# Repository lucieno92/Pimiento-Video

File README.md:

# Suite Post-Production — Prototype

Application desktop regroupant plusieurs outils de post-production dans
une seule interface, avec une page d'accueil pour naviguer entre les
modules.

## Modules disponibles dans ce prototype

- **Téléchargement multiplateforme** : télécharge vidéos/audio depuis
  YouTube, TikTok, Facebook, Instagram, Vimeo, etc. (basé sur yt-dlp).
- **Métadonnées (rush)** : glisser un fichier vidéo pour voir toutes ses
  métadonnées techniques (codec, résolution, frame rate, profondeur de
  couleur, sous-échantillonnage chroma, pistes audio, sous-titres...),
  basé sur pymediainfo (équivalent du logiciel MediaInfo).
- **Encodeur** (type Shutter Encoder) : glisser une ou plusieurs vidéos,
  choisir une catégorie (montage, diffusion/broadcast, web, audio seul,
  suite d'images, réencapsulation), un format précis, ajuster résolution
  et frame rate (préréglages ou valeurs personnalisées), prévisualiser le
  rush sélectionné, et lancer l'encodage. Basé directement sur FFmpeg.
- **Transcription** : glisser un fichier audio/vidéo, choisir la langue,
  transcrire en local avec Whisper (faster-whisper), puis exporter en
  TXT/DOCX/PDF ou en sous-titres SRT/VTT (nombre de mots par sous-titre
  réglable). 100% autonome, aucun compte tiers requis.

## Installation

### 1. Python
Il faut Python 3.10 ou plus récent : https://www.python.org/downloads/
(cocher "Add python.exe to PATH" pendant l'installation).

### 2. FFmpeg et MediaInfo
Rien à installer séparément : les deux sont embarqués automatiquement
via les paquets Python `imageio-ffmpeg` et `pymediainfo`, installés à
l'étape suivante.

### 3. Dépendances Python
Dans le dossier du projet :

```bash
python3 -m venv venv
source venv/bin/activate        # Sur Windows : venv\Scripts\activate
pip install -r requirements.txt
```

## Lancer l'application

```bash
python3 main.py
```

Une page d'accueil s'ouvre avec une carte par module. Clique sur celui
que tu veux utiliser.

## Structure du projet

```
main.py                    -> point d'entrée, assemble les pages
core/
  ffmpeg_utils.py           -> détection FFmpeg (partagée par tous les modules)
  settings_store.py         -> préférences persistantes (registre Windows / plist Mac)
pages/
  home_page.py              -> page d'accueil avec les cartes de modules
  downloader_page.py        -> module Téléchargement multiplateforme
  mediainfo_page.py         -> module Métadonnées (type MediaInfo)
  encoder_page.py           -> module Encodeur (type Shutter Encoder)
  transcription_page.py     -> module Transcription (Whisper local)
  settings_page.py          -> paramètres avancés (dépannage FFmpeg), caché par défaut
```

## Note sur la Transcription (téléchargement de modèle)

Au premier lancement d'une transcription, Whisper télécharge le modèle
choisi (quelques centaines de Mo à plus d'1 Go selon la taille du modèle) —
il faut donc une connexion internet la première fois, sans création de
compte. Les lancements suivants avec le même modèle sont locaux et plus
rapides.

## Paramètres avancés (FFmpeg)

Dans l'immense majorité des cas, tout fonctionne sans rien configurer.
Si jamais un souci technique persiste, un petit bouton ⚙ discret en bas
à droite de la page d'accueil permet d'indiquer manuellement où se
trouve FFmpeg sur la machine. Ce n'est qu'un filet de sécurité — pas une
étape normale d'utilisation.

## Limitations connues de ce prototype

- Pas encore de file d'attente persistante pour les téléchargements.
- Pas encore de gestion de profils/préréglages sauvegardés.
- Le module Métadonnées met en avant les champs les plus utiles en
  post-prod (codec, résolution, frame rate, bit depth, chroma
  subsampling...) ; pour les caméras qui embarquent des informations
  spécifiques (profil LOG, LUT, timecode...), elles restent consultables
  dans la section "métadonnées brutes" si la caméra les a enregistrées
  dans le fichier — toutes les caméras ne le font pas systématiquement.
- Pas encore packagé en `.exe` / `.app` — pour l'instant ça se lance avec
  Python installé. `imageio-ffmpeg` et `pymediainfo` fournissent tous
  les deux des hooks PyInstaller, donc leur contenu embarqué sera
  automatiquement inclus dans l'exécutable final le moment venu.

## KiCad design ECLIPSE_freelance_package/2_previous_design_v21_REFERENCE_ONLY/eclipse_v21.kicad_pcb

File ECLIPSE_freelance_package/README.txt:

ECLIPSE - PCB design package
Breloque - August 2026

--------------------------------------------------------------------
WHAT IS IN THIS PACKAGE
--------------------------------------------------------------------

1_brief/
    ECLIPSE_PCB_brief_EN.pdf    <- START HERE. The full brief in English.
    ECLIPSE_PCB_brief_FR.pdf       Same document in French.

2_previous_design_v21_REFERENCE_ONLY/
    The KiCad project of the board I designed myself and that FAILED.
    Provided as documentation only - see the warning below.

--------------------------------------------------------------------
IMPORTANT - ABOUT THE PREVIOUS DESIGN
--------------------------------------------------------------------

The KiCad project in folder 2 is the board that was manufactured,
assembled in 5 units, and DESTROYED on first power-up.

It is included so you can see what was intended functionally, and so
you can verify for yourself the faults listed in section 4 of the
brief - several of them are measurable directly in these files.

DO NOT reuse this design as a starting point. It contains, among
other issues, a regulator enable pin tied to 12 V on a pin rated 6 V
absolute maximum, unconnected microcontroller strapping pins, and a
module footprint that cannot be inspected or reworked.

You are expected to redesign from scratch. You are entirely free on
components, architecture and values.

--------------------------------------------------------------------
HOW TO OPEN THE PREVIOUS DESIGN
--------------------------------------------------------------------

Open  eclipse_v21.kicad_pro  in KiCad (version 8 or newer).

The project is self-contained: the footprint library (eclipse.pretty)
and the symbol library (easyeda2kicad.kicad_sym) are included in the
same folder, and fp-lib-table / sym-lib-table point to them with
relative paths. Nothing else needs to be installed.

Board: 58 x 24 mm, 2 layers, FR-4, 1.6 mm.

BOM_eclipse_v21.csv and CPL_eclipse_v21.csv are the bill of materials
and pick-and-place files that were used for assembly (JLCPCB format).

--------------------------------------------------------------------
NOT INCLUDED
--------------------------------------------------------------------

- Gerber files: not included, as they describe the failed board and
  are of no use for a new design. They can be regenerated from the
  KiCad project if you want to look at them.

- Firmware: I supply it separately once the hardware is defined.

- BRELOQUE logo: high-resolution file supplied on request, for the
  silkscreen.

- LED strip datasheet: available on request. Please ask for it before
  sizing the LED channels - see the note in section 3 of the brief.

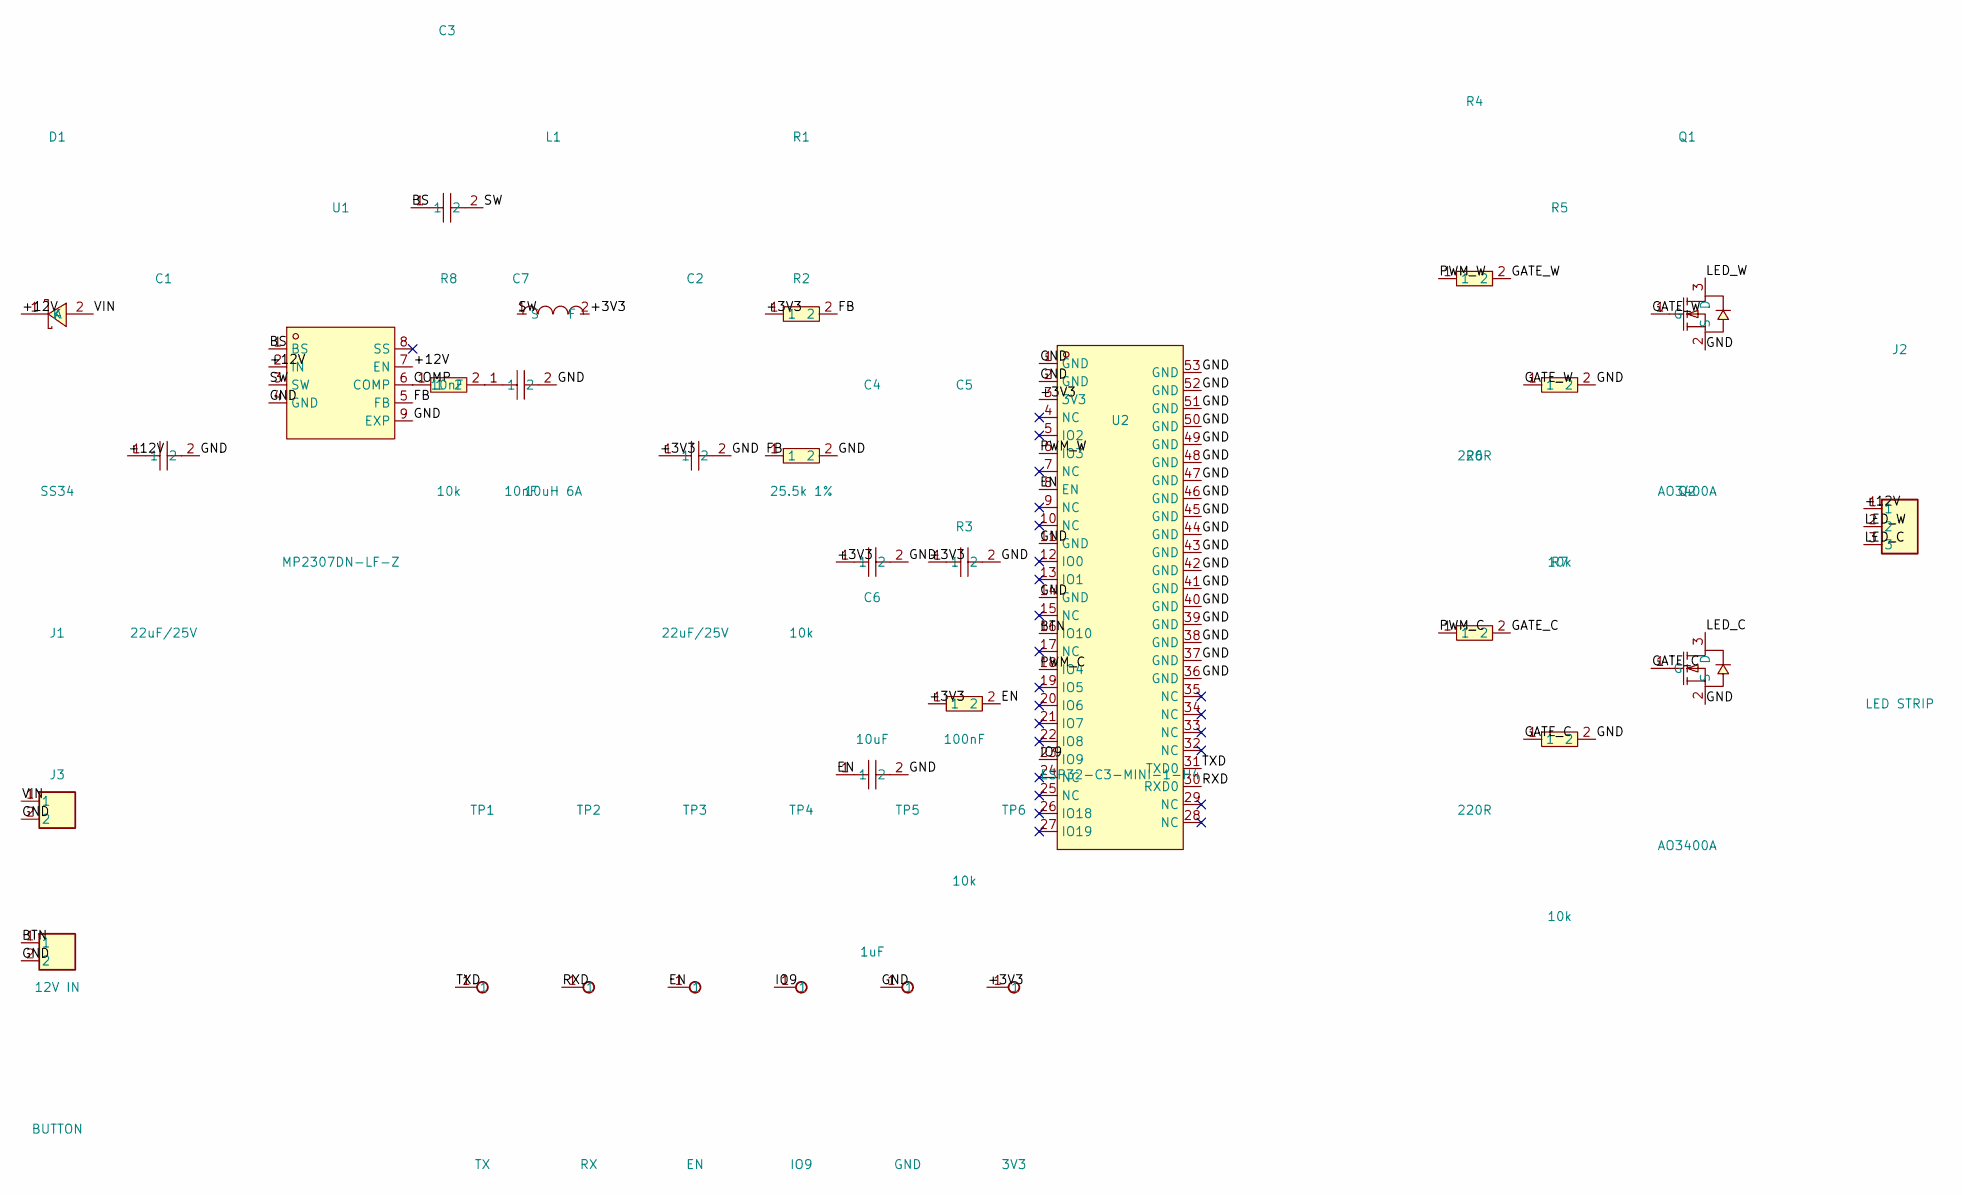
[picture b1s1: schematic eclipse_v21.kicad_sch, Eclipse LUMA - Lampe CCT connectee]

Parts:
C1: 22uF/25V; C1206; LCSC C12891
C2: 22uF/25V; C0805; LCSC C45783
C3, C7: 10nF; C0402; LCSC C15195
C4: 10uF; C0805; LCSC C15850
C5: 100nF; C0603; LCSC C14663
C6: 1uF; C0402; LCSC C52923
D1: SS34; SMA_L4.3-W2.6-LS5.2-RD; LCSC C8678
J1: 12V IN; SolderPad2
J2: LED STRIP; SolderPad3
J3: BUTTON; SolderPad2
L1: 10uH 6A; IND-SMD_L7.0-W6.6; LCSC C237927
Q1, Q2: AO3400A; SOT-23-3_L2.9-W1.3-P1.90-LS2.4-BR; LCSC C20917
R1: 25.5k 1%; R0603; LCSC C273793
R2, R3, R5, R7, R8: 10k; R0603; LCSC C25804
R4, R6: 220R; R0603; LCSC C22962
TP1: TX; TP
TP2: RX; TP
TP3: EN; TP
TP4: IO9; TP
TP5: GND; TP
TP6: 3V3; TP
U1: MP2307DN-LF-Z; SOP-8_L4.9-W3.9-P1.27-LS6.0-BL-EP; LCSC C18921
U2: ESP32-C3-MINI-1-H4; WIFIM-SMD_ESP32-C3-MINI-1; LCSC C2934569

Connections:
/+3V3: C2.1, C4.1, C5.1, L1.2 (F), R1.1, R3.1, TP6.1 (1_1), U2.3 (3V3)
/+12V: C1.1, D1.1 (K), J2.1, U1.2 (IN), U1.7 (EN)
/BS: C3.1, U1.1 (BS)
/BTN: J3.1, U2.16 (IO10)
/COMP: R8.1, U1.6 (COMP)
/EN: C6.1, R3.2, TP3.1 (1_1), U2.8 (EN)
/FB: R1.2, R2.1, U1.5 (FB)
/GATE_C: Q2.1 (G), R6.2, R7.1
/GATE_W: Q1.1 (G), R4.2, R5.1
/GND: C1.2, C2.2, C4.2, C5.2, C6.2, C7.2, J1.2, J3.2, Q1.2 (S), Q2.2 (S), R2.2, R5.2, R7.2, TP5.1 (1_1), U1.4 (GND), U1.9 (EXP), U2.1 (GND), U2.2 (GND), U2.11 (GND), U2.14 (GND), U2.36 (GND), U2.37 (GND), U2.38 (GND), U2.39 (GND), U2.40 (GND), U2.41 (GND), U2.42 (GND), U2.43 (GND), U2.44 (GND), U2.45 (GND), U2.46 (GND), U2.47 (GND), U2.48 (GND), U2.49 (GND), U2.50 (GND), U2.51 (GND), U2.52 (GND), U2.53 (GND)
/IO9: TP4.1 (1_1), U2.23 (IO9)
/LED_C: J2.3, Q2.3 (D)
/LED_W: J2.2, Q1.3 (D)
/PWM_C: R6.1, U2.18 (IO4)
/PWM_W: R4.1, U2.6 (IO3)
/RXD: TP2.1 (1_1), U2.30 (RXD0)
/SW: C3.2, L1.1 (S), U1.3 (SW)
/TXD: TP1.1 (1_1), U2.31 (TXD0)
/VIN: D1.2 (A), J1.1
unnamed: C7.1, R8.2

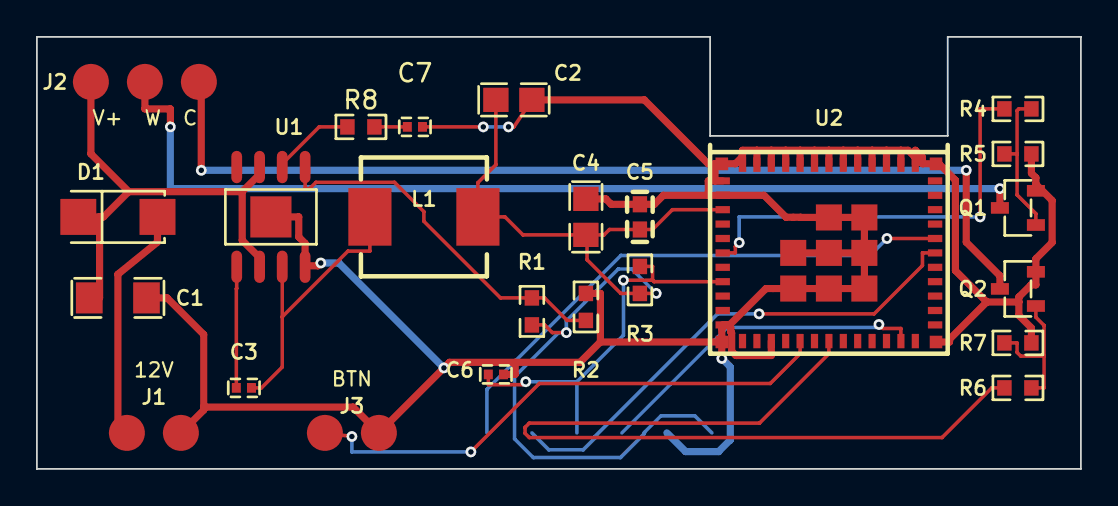
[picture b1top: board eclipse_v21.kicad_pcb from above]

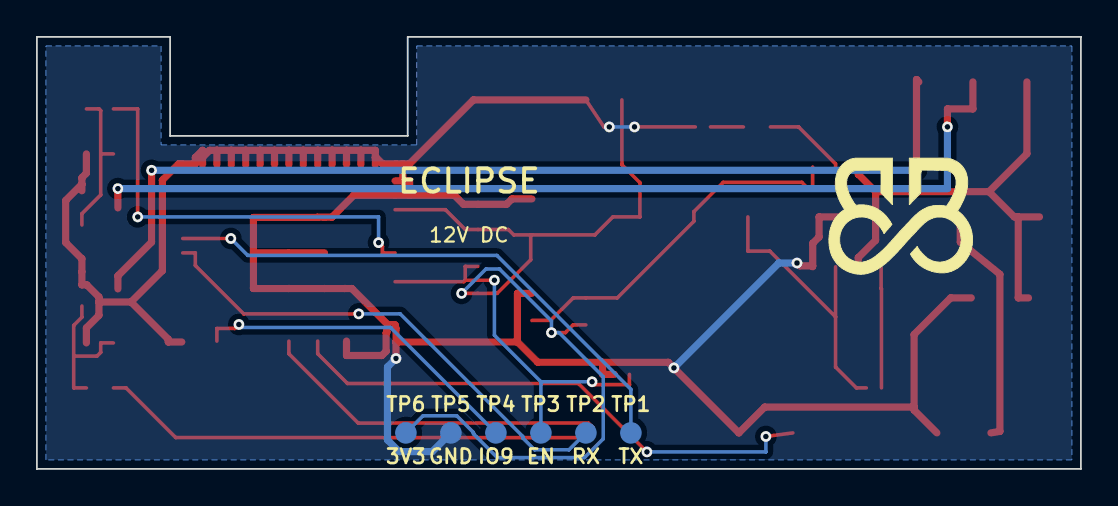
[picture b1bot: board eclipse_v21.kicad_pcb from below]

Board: 2 copper layers, 58.0 x 24.0 mm, 30 parts (6 on the bottom side), 20 nets.
